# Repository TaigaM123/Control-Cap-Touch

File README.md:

# Control-Cap-Touch
Thanks to KiCAD and Digikey for the majority of the footprints <br>
Adafruit has been really helpful with Capacitive Touch related stuff

Disclaimer: This is by no means a complete or accurate design. Please do not use this as reference material. If you want to contribute, please go ahead! I know I've made a lot of mistakes and it would be great if someone more knowledgeable than myself pointed them out and fixed them!

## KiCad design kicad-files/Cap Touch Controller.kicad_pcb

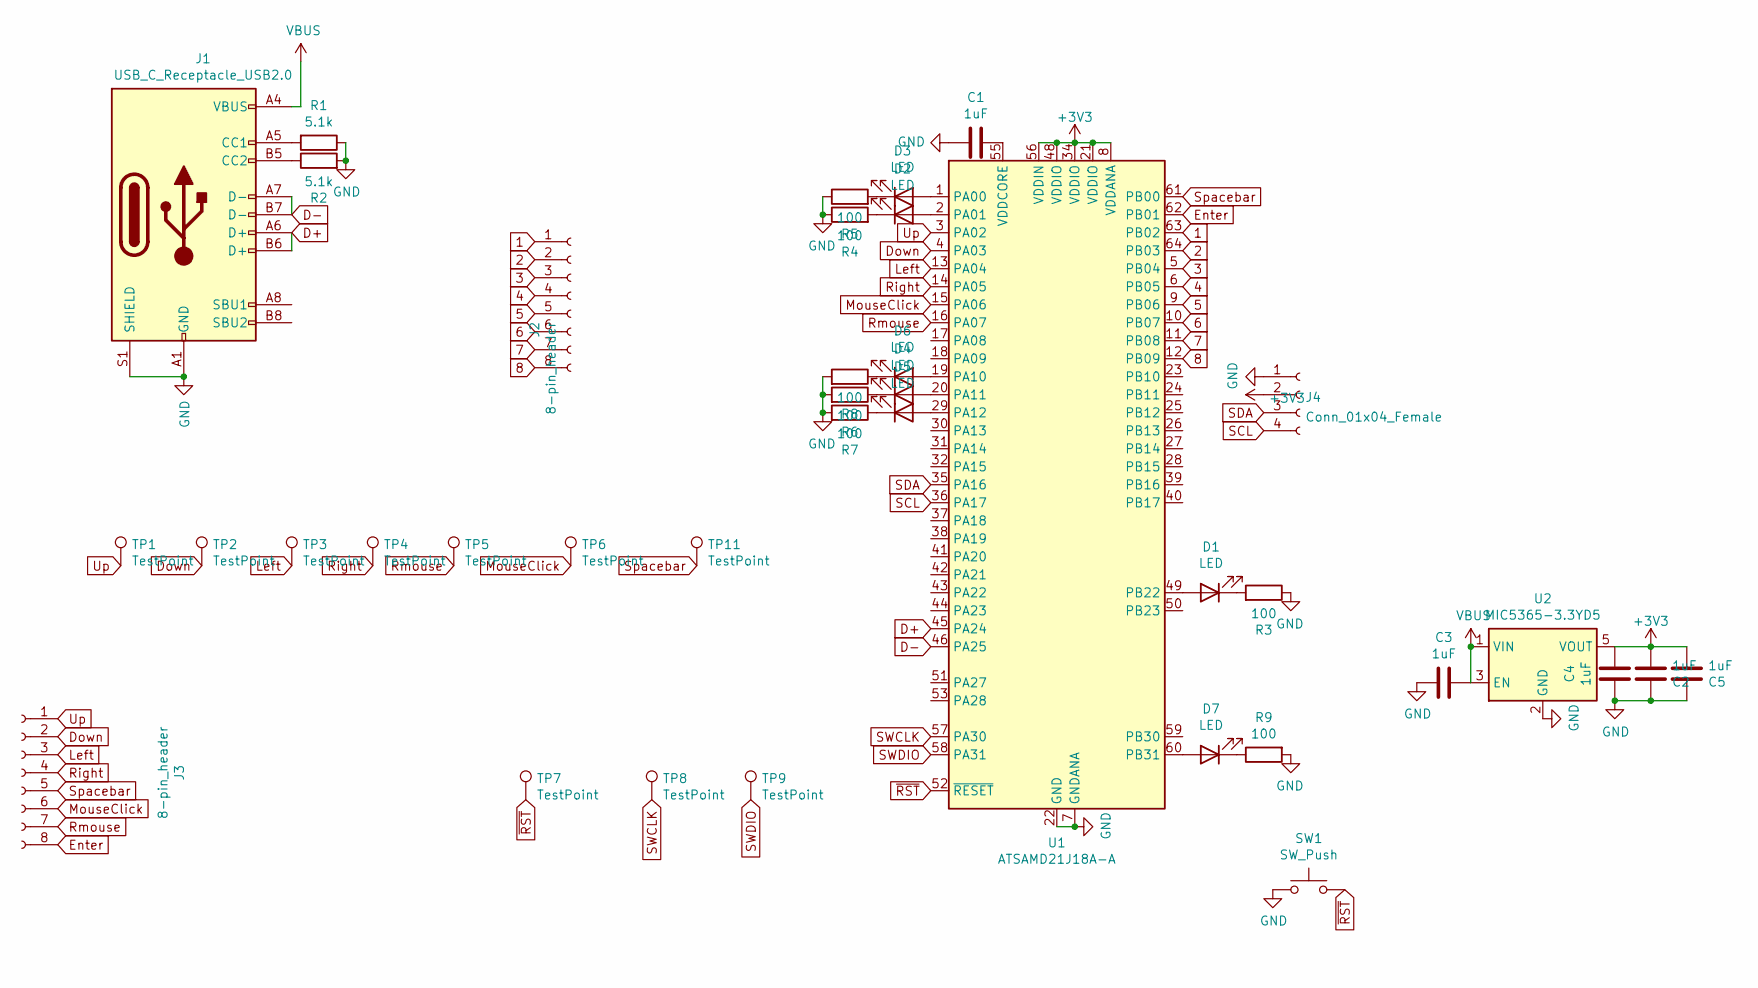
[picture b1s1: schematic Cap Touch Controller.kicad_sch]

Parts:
C1, C2, C3, C4, C5: 1uF; C_0603_1608Metric_Pad1.08x0.95mm_HandSolder
D1, D2, D3, D4, D5, D6, D7: LED; LED_0603_1608Metric_Castellated
J1: USB_C_Receptacle_USB2.0; USB_C_Receptacle_HRO_TYPE-C-31-M-12
J2, J3: 8-pin_header; PinSocket_1x08_P2.54mm_Vertical
J4: Conn_01x04_Female; JST_SH_SM04B-SRSS-TB_1x04-1MP_P1.00mm_Horizontal
R1, R2: 5.1k; R_0603_1608Metric_Pad0.98x0.95mm_HandSolder
R3, R4, R5, R6, R7, R8, R9: 100; R_0603_1608Metric_Pad0.98x0.95mm_HandSolder
SW1: SW_Push; SW_SPST_PTS645
TP1, TP2, TP3, TP4: TestPoint; Arrow_Gator
TP5, TP6: TestPoint; Circular_Gator
TP7, TP8, TP9: TestPoint; TestPoint_Pad_D1.0mm
TP11: TestPoint; Gator
U1: ATSAMD21J18A-A; TQFP-64_10x10mm_P0.5mm
U2: MIC5365-3.3YD5; SOT-23-5

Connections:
1: J2.1, U1.63 (PB02)
2: J2.2, U1.64 (PB03)
3: J2.3, U1.5 (PB04)
4: J2.4, U1.6 (PB05)
5: J2.5, U1.9 (PB06)
6: J2.6, U1.10 (PB07)
7: J2.7, U1.11 (PB08)
8: J2.8, U1.12 (PB09)
+3V3: C2.2, C4.1, C5.2, J4.2, U1.8 (VDDANA), U1.21 (VDDIO), U1.34 (VDDIO), U1.48 (VDDIO), U1.56 (VDDIN), U2.5 (VOUT)
D+: J1.A6 (D+), J1.B6 (D+), U1.45 (PA24)
D-: J1.A7 (D-), J1.B7 (D-), U1.46 (PA25)
Down: J3.2, TP2.1, U1.4 (PA03)
Enter: J3.8, U1.62 (PB01)
GND: C1.1, C2.1, C3.2, C4.2, C5.1, J1.A1 (GND), J1.A12 (GND), J1.B1 (GND), J1.B12 (GND), J1.S1 (SHIELD), J4.1, R1.1, R2.2, R3.1, R4.1, R5.1, R6.2, R7.2, R8.2, R9.2, SW1.1, U1.7 (GNDANA), U1.22 (GND), U1.33 (GND), U1.47 (GND), U1.54 (GND), U2.2 (GND)
Left: J3.3, TP3.1, U1.13 (PA04)
MouseClick: J3.6, TP6.1, U1.15 (PA06)
unnamed: C1.2, U1.55 (VDDCORE)
unnamed: D1.1 (K), R3.2
unnamed: D1.2 (A), U1.49 (PB22)
unnamed: D2.1 (K), R4.2
unnamed: D2.2 (A), U1.2 (PA01)
unnamed: D3.1 (K), R5.2
unnamed: D3.2 (A), U1.1 (PA00)
unnamed: D4.1 (K), R6.1
unnamed: D4.2 (A), U1.20 (PA11)
unnamed: D5.1 (K), R7.1
unnamed: D5.2 (A), U1.29 (PA12)
unnamed: D7.1 (K), R9.1
unnamed: D7.2 (A), U1.60 (PB31)
unnamed: J1.A5 (CC1), R1.2
unnamed: J1.B5 (CC2), R2.1
unnamed: D6.1 (K), R8.1
unnamed: D6.2 (A), U1.19 (PA10)
Right: J3.4, TP4.1, U1.14 (PA05)
Rmouse: J3.7, TP5.1, U1.16 (PA07)
SCL: J4.4, U1.36 (PA17)
SDA: J4.3, U1.35 (PA16)
SWCLK: TP8.1, U1.57 (PA30)
SWDIO: TP9.1, U1.58 (PA31)
Spacebar: J3.5, TP11.1, U1.61 (PB00)
Up: J3.1, TP1.1, U1.3 (PA02)
VBUS: C3.1, J1.A4 (VBUS), J1.A9 (VBUS), J1.B4 (VBUS), J1.B9 (VBUS), U2.1 (VIN), U2.3 (EN)
~RST: SW1.2, TP7.1, U1.52 (~RESET)

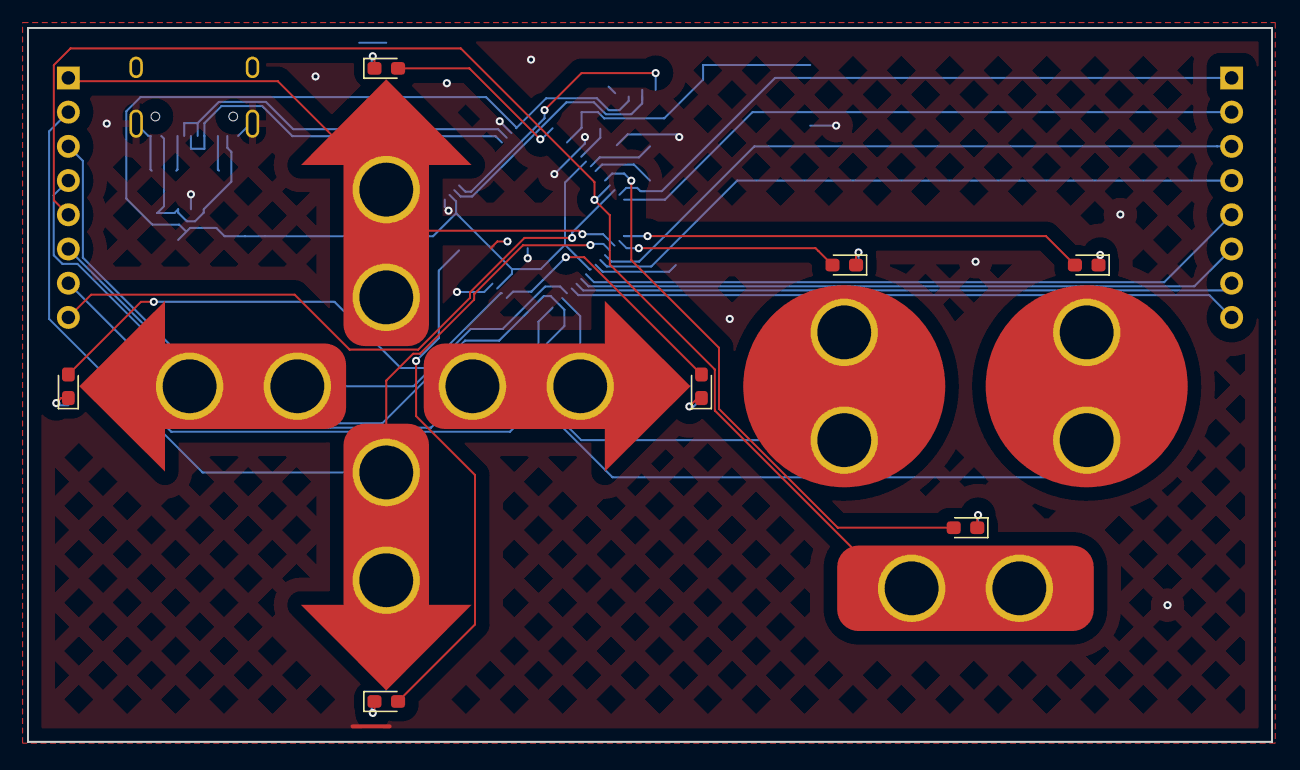
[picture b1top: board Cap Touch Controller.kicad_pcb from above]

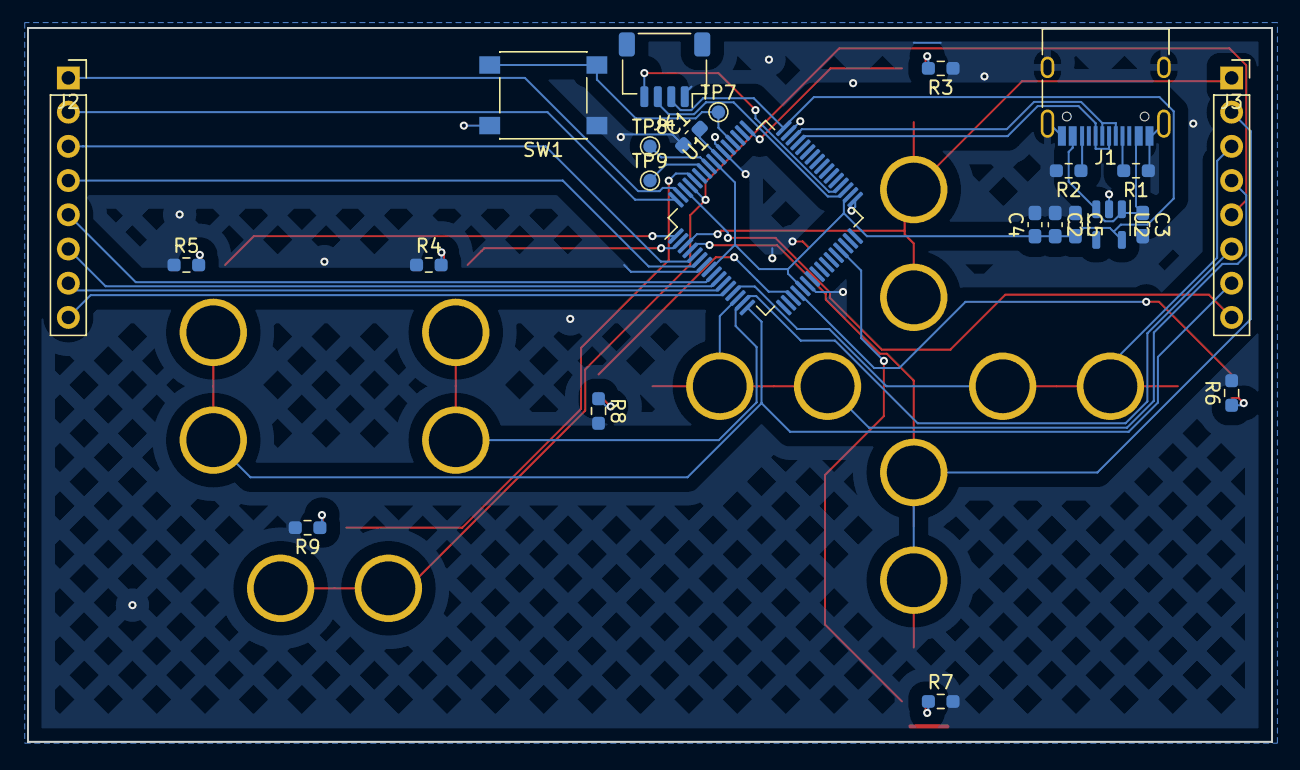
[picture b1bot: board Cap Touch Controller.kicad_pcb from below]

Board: 2 copper layers, 92.4 x 53.0 mm, 38 parts (24 on the bottom side), 43 nets.

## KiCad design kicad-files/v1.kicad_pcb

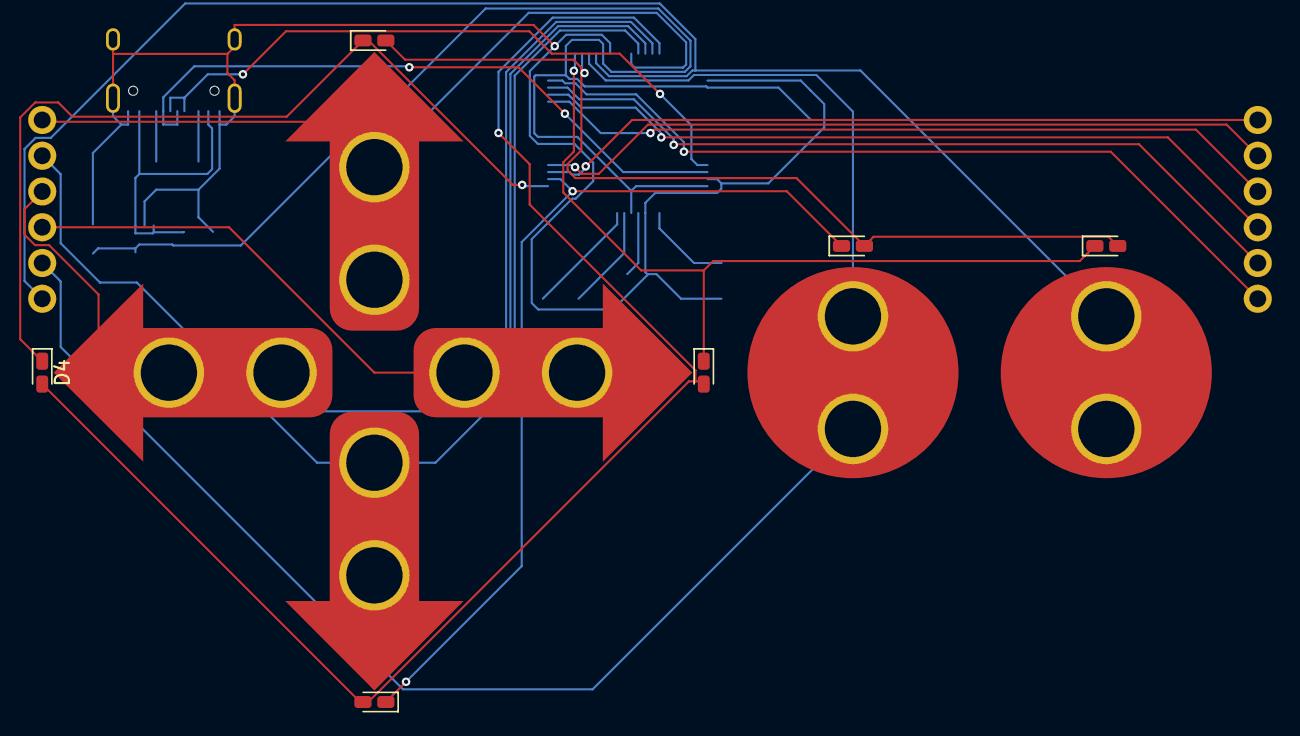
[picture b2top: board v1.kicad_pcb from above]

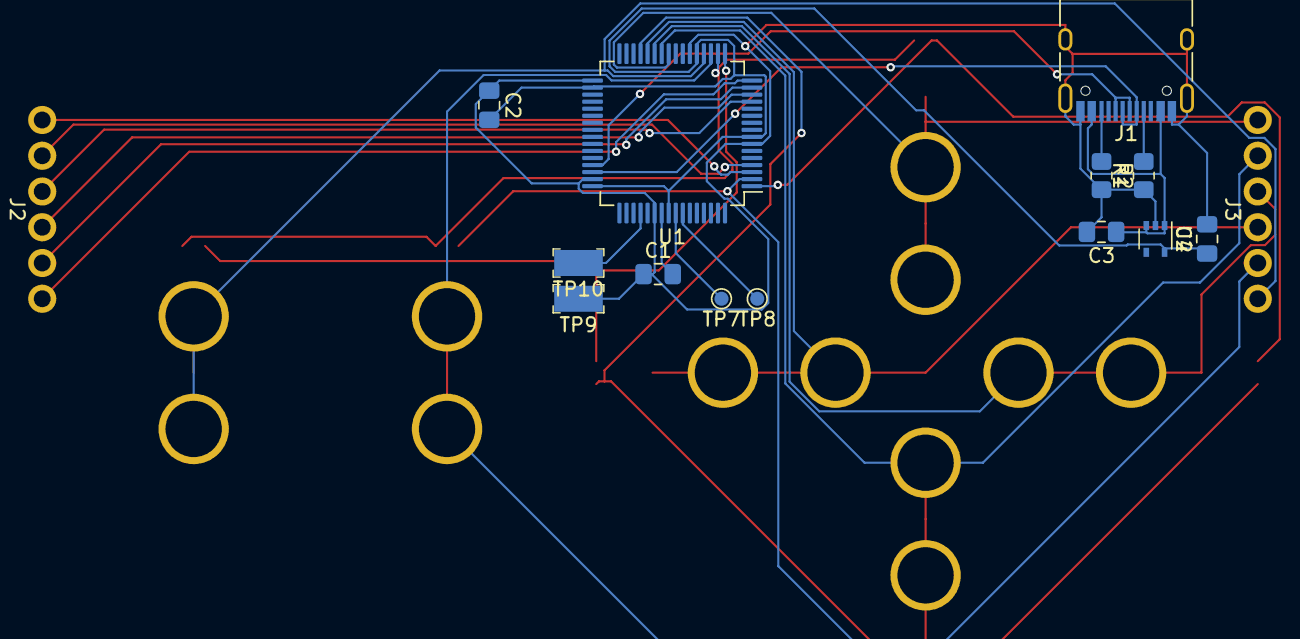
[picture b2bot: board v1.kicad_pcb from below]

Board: 2 copper layers, 27 parts (15 on the bottom side), 28 nets.

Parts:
C1, C2, C3, C4: 1uF; C_0805_2012Metric_Pad1.18x1.45mm_HandSolder
D1, D2, D3, D4, D5, D6: LED; LED_0603_1608Metric_Castellated
J1: USB_C_Receptacle_USB2.0; USB_C_Receptacle_HRO_TYPE-C-31-M-12
J2, J3: 6-pin_header; 6-pinheader
R1, R2: 5.1k; R_0805_2012Metric_Pad1.20x1.40mm_HandSolder
TP1, TP2, TP3, TP4: TestPoint; Arrow_Gator
TP5, TP6: TestPoint; Circular_Gator
TP7, TP8: TestPoint; TestPoint_Pad_D1.0mm
TP9, TP10: TestPoint; PC_TEST_POINT_SMD
U1: ATSAMD21J15B-A; TQFP-64_10x10mm_P0.5mm
U2: MIC5365-3.3YC5; SOT-353_SC-70-5

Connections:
+3V3: C2.2, C4.1, U1.8, U1.21, U1.34, U1.48, U1.56, U2.5
+5V: C3.1, J1.A4, J1.A9, J1.B4, J1.B9, U2.1, U2.3
/1: J2.1, U1.3
/2: J2.2, U1.4
/3: J2.3, U1.13
/4: J2.4, U1.14
/5: J2.5, U1.15
/6: J2.6, U1.16
/SWCLK: TP7.1, U1.57
/SWDIO: TP8.1, U1.58
D+: J1.A6, J1.B6, U1.45
D-: J1.A7, J1.B7, U1.46
Down: J3.2, TP2.1, U1.26
GND: C1.1, C2.1, C3.2, C4.2, J1.A1, J1.A12, J1.B1, J1.B12, J1.S1, R1.1, R2.2, TP9.1, U1.7, U1.22, U1.33, U1.47, U1.54, U2.2
LED_1: D1.1, D4.1, U1.1
LED_2: D2.1, D5.1, U1.2
LED_3: D3.1, D6.1, U1.17
LED_A: D1.2, D2.2, D3.2, U1.18
LED_B: D4.2, D5.2, D6.2, U1.29
Left: J3.3, TP3.1, U1.27
MouseClick: J3.6, TP6.1, U1.20
unnamed: C1.2, U1.55
unnamed: J1.A5, R1.2
unnamed: J1.B5, R2.1
Right: J3.4, TP4.1, U1.28
Spacebar: J3.5, TP5.1, U1.19
Up: J3.1, TP1.1, U1.25
~RST: TP10.1, U1.52

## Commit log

2021-11-28 Create delete
2021-12-21 New Files
2021-12-21 More deletions
2021-12-21 Last deletion for now
2021-12-21 Delete Cap Touch Controller.net
    Oops, forgot about this one
2021-12-21 2.8 volts
2021-12-24 Updated Files
2021-12-31 KiCad 6 files
2022-04-21 Added Files
2022-04-21 Fix gitignore
2022-06-18 Changed files
